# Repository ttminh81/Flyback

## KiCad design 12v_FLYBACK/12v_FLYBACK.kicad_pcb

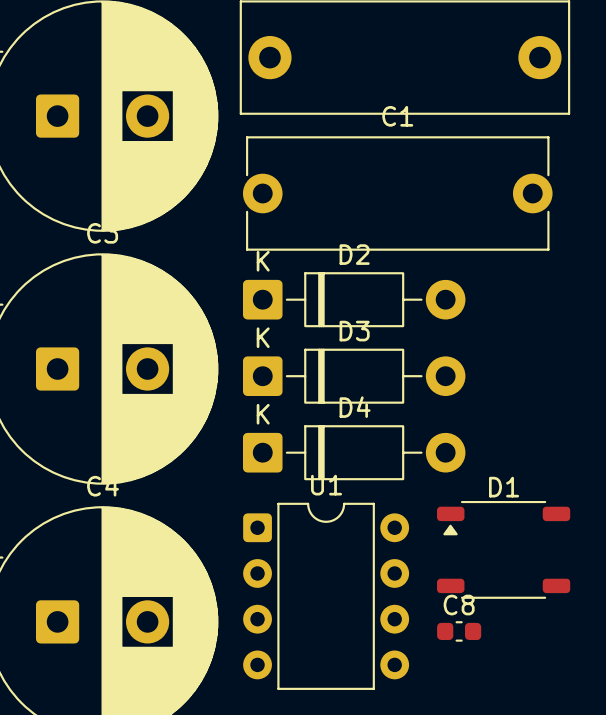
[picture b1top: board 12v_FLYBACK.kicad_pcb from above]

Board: 2 copper layers, 11 parts (0 on the bottom side), 7 nets, no tracks yet.

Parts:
C1: C/0.1uF/275VAC; C_Rect_L16.5mm_W6.0mm_P15.00mm_MKT
C2, C3, C4: CP/22uF/450V; CP_Radial_D12.5mm_P5.00mm
C5: C/220nF/400VDC; C_Rect_L18.0mm_W6.0mm_P15.00mm_FKS3_FKP3
C8: C0603/100nF; C_0603_1608Metric
D1: MDB8S; TSSOP-4_4.4x5mm_P4mm
D2, D3: 1N4007; D_DO-41_SOD81_P10.16mm_Horizontal
D4: US1M; D_DO-41_SOD81_P10.16mm_Horizontal
U1: DIP-8_W7.62mm

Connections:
unnamed: C2.1, D1.1 (+)
unnamed: C2.2, C3.2, C4.2, D1.2 (-)
unnamed: D2.2 (A), U1.5 (DRAIN), U1.6 (DRAIN), U1.7 (DRAIN), U1.8 (DRAIN)
unnamed: C5.2, D2.1 (K)
unnamed: C8.1, D3.1 (K)
unnamed: D4.1 (K), U1.1 (VDD)
unnamed: C3.1, C4.1, C5.1

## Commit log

2025-03-24 Kicad and Document
2025-03-24 Schematic done
2025-03-25 New update
2025-04-09 Change symbol
2026-01-21 New Schematic
2026-01-28 Change controller IC
